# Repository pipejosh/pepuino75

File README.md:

## Introducing the pepuino75

This is the pepuino75, a 75 percent keyboard, featuring my custom microcontroler, the pepuinoNanoV1 (https://github.com/pipejosh/pepuinoNano-devBoard), this keyboard also features a rotary encoder, design to make it as compact as possible, without lossing any of its features!

### RENDER
 
### SCHEMATIC
 
### PCB
 
### CASE

### BOM

## KIT Components

| Item | Description | Quantity | Unit Price | Total Price | URL |
|---|---|---:|---:|---:|---|
| Keycaps Set | Keycaps for the keyboard | 126 | 0.07 | 8.31 | https://www.aliexpress.com/item/1005007321700850.html |
| Switches | Mechanical switches | 90 | 0.20 | 18.11 | https://www.aliexpress.com/item/1005009787231480.html |
| Diodes | SMD diodes | 100 | 0.03 | 3.15 | https://www.aliexpress.com/item/1005007160563285.html |
| USB-C Cable | USB-C cable | 1 | 3.31 | 3.31 | https://www.aliexpress.com/item/1005005080440661.html |
| M2 Standoff | M2 standoff 5 mm | 50 | 0.05 | 2.50 | https://www.aliexpress.com/item/1005006049595637.html |
| M2 Screw | M2 screw 5 mm | 50 | 0.03 | 1.60 | https://www.aliexpress.com/item/1005005070119421.html |
| Stabilizers | MX stabilizers (6.25u & 2u) | 5 | 0.73 | 3.64 | https://www.aliexpress.com/item/1005007212869086.html |
| Taxes | AliExpress tax | — | — | 4.28 | — |

**KIT Components Subtotal:** 44.90

---

## PCB Costs

| Item | Description | Cost |
|---|---|---:|
| JLCPCB | Pepuino75 PCB | 26.47 |
| JLCPCB Shipping | PCB shipping + taxes | 21.58 |

**PCB Subtotal:** 48.05

---

## GRAND TOTAL

| Category | Amount |
|---|---:|
| KIT Components | 44.90 |
| PCB | 48.05 |
| **TOTAL** | **92.95** |

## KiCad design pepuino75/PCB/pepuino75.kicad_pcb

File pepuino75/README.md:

## Introducing the pepuino75

This is the pepuino75, a 75 percent keyboard, featuring my custom microcontroler, the pepuinoNanoV1, this keyboard also features a rotary encoder, design to make it as compact as possible, without lossing any of its features!

### BOM
 
### SCHEMATIC
 
### PCB
 
### RENDER

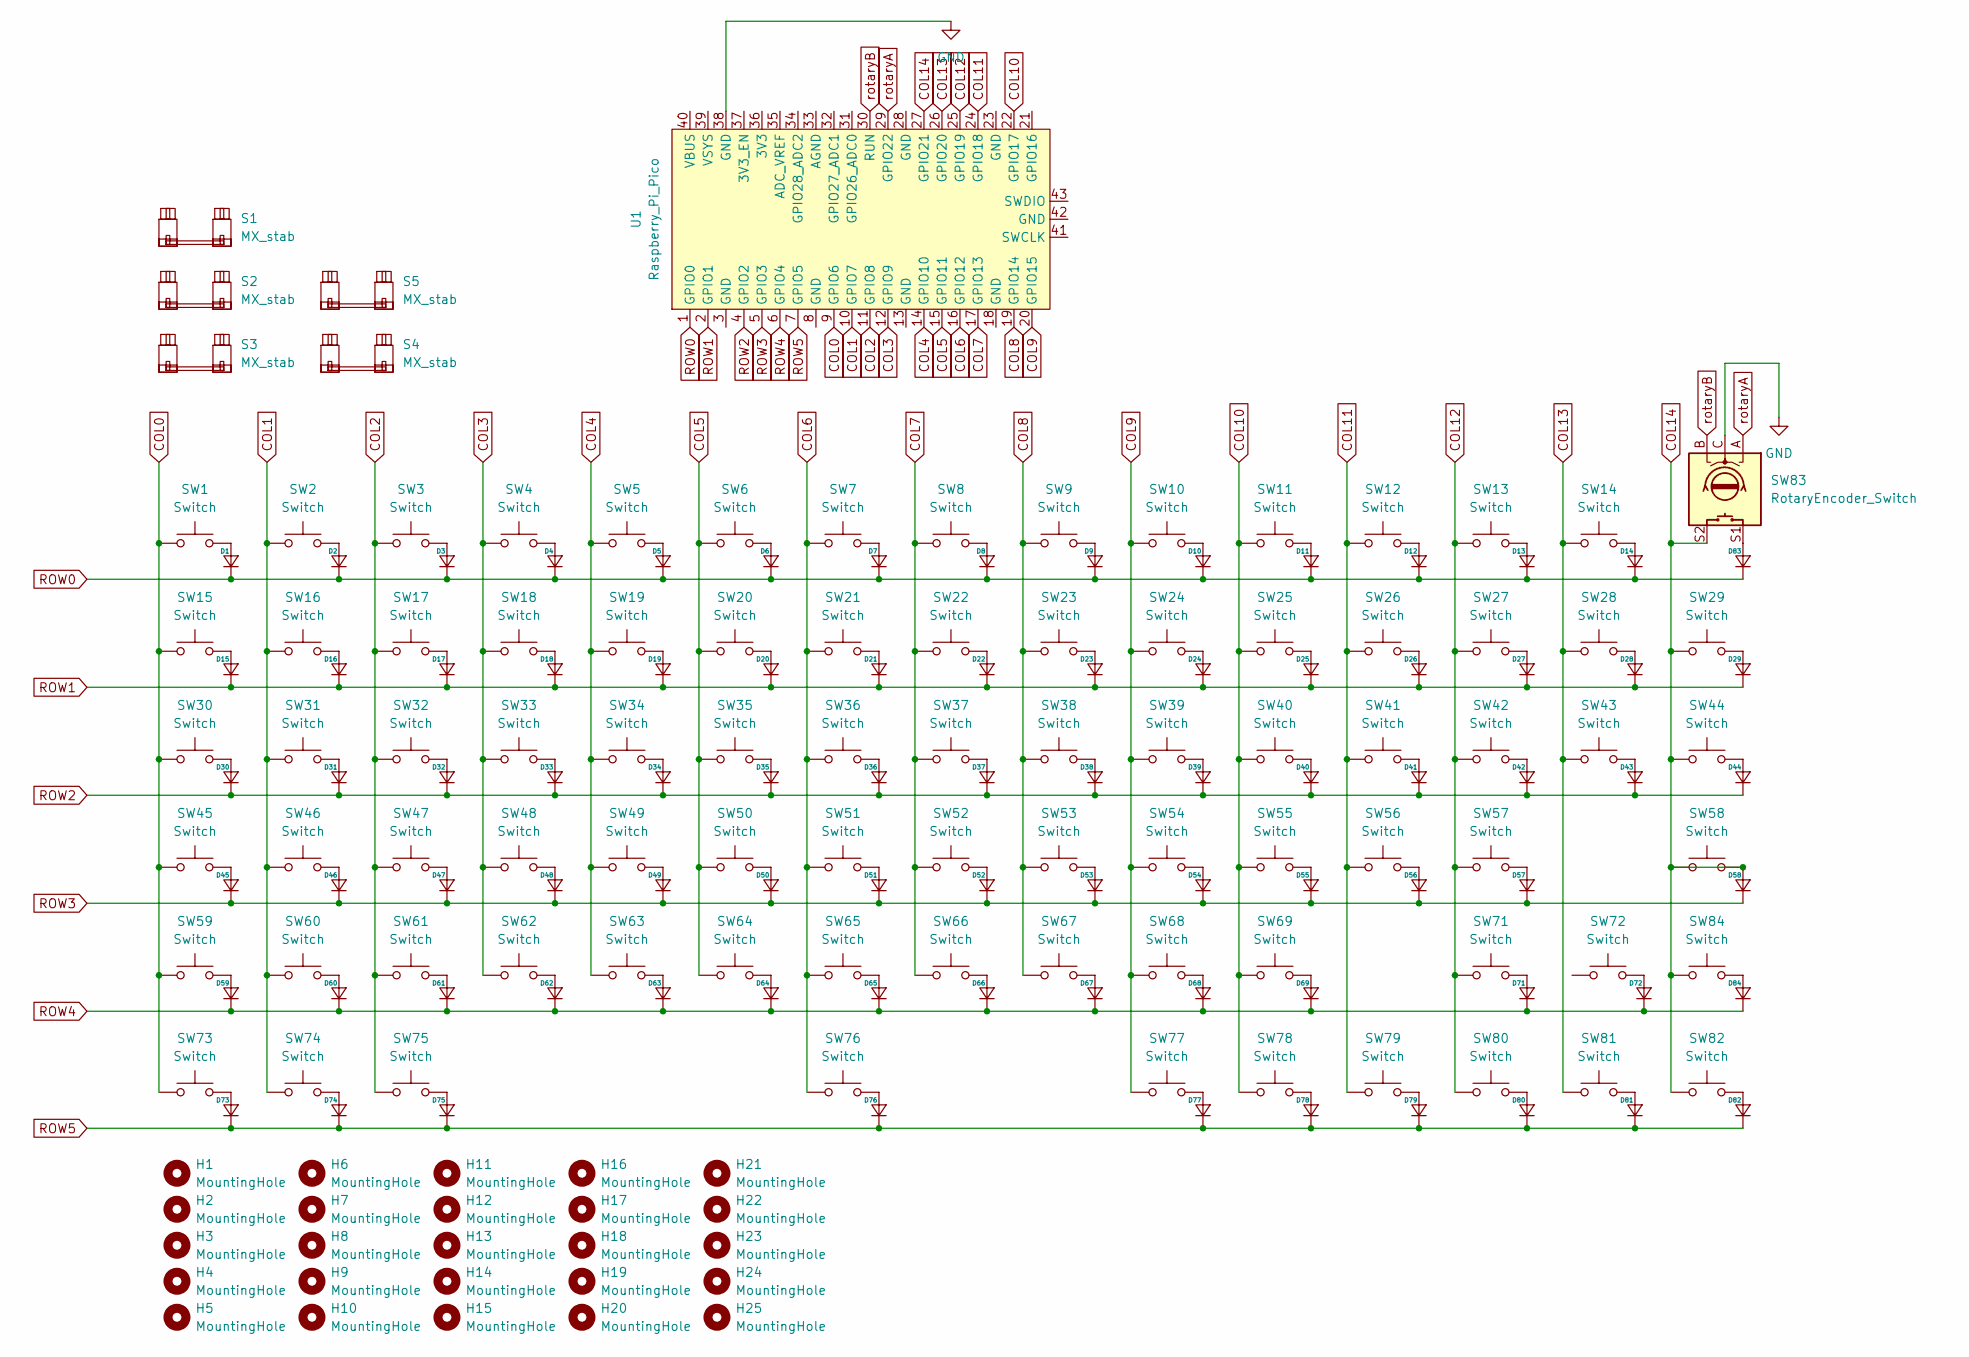
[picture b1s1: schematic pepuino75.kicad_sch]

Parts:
D1, D2, D3, D4, D5, D6, D7, D8, D9, D10, D11, D12, D13, D14, D15, D16, D17, D18, D19, D20, D21, D22, D23, D24, D25, D26, D27, D28, D29, D30, D31, D32, D33, D34, D35, D36, D37, D38, D39, D40, D41, D42, D43, D44, D45, D46, D47, D48, D49, D50, D51, D52, D53, D54, D55, D56, D57, D58, D59, D60, D61, D62, D63, D64, D65, D66, D67, D68, D69, D71, D72, D73, D74, D75, D76, D77, D78, D79, D80, D81, D82, D83, D84: Diode_SOD-123
H1, H2, H3, H4, H5, H6, H7, H8, H9, H10, H11, H12, H13, H14, H15, H16, H17, H18, H19, H20, H21, H22, H23, H24, H25: MountingHole; MountingHole_2.2mm_M2
S1: MX_stab; Stabilizer_MX_6.25u
S2, S3, S4, S5: MX_stab; Stabilizer_MX_2.00u
SW1, SW2, SW3, SW4, SW5, SW6, SW7, SW8, SW9, SW10, SW11, SW12, SW13, SW14, SW15, SW16, SW17, SW18, SW19, SW20, SW21, SW22, SW23, SW24, SW25, SW26, SW27, SW29, SW31, SW32, SW33, SW34, SW35, SW36, SW37, SW38, SW39, SW40, SW41, SW42, SW44, SW46, SW47, SW48, SW49, SW50, SW51, SW52, SW53, SW54, SW55, SW56, SW58, SW60, SW61, SW62, SW63, SW64, SW65, SW66, SW67, SW68, SW69, SW72, SW77, SW78, SW79, SW80, SW81, SW82, SW84: Switch; MX_PCB_1.00u
SW28: Switch; MX_PCB_2.00u
SW30, SW43: Switch; MX_PCB_1.50u
SW45, SW71: Switch; MX_PCB_1.75u
SW57, SW59: Switch; MX_PCB_2.25u
SW73, SW74, SW75: Switch; MX_PCB_1.25u
SW76: Switch; MX_PCB_6.25u
SW83: RotaryEncoder_Switch; ROT_Alps_EC11E-Switch
U1: Raspberry_Pi_Pico

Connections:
COL0: SW1.1, SW15.1, SW30.1, SW45.1, SW59.1, SW73.1, U1.9 (GPIO6)
COL1: SW2.1, SW16.1, SW31.1, SW46.1, SW60.1, SW74.1, U1.10 (GPIO7)
COL2: SW3.1, SW17.1, SW32.1, SW47.1, SW61.1, SW75.1, U1.11 (GPIO8)
COL3: SW4.1, SW18.1, SW33.1, SW48.1, SW62.1, U1.12 (GPIO9)
COL4: SW5.1, SW19.1, SW34.1, SW49.1, SW63.1, U1.14 (GPIO10)
COL5: SW6.1, SW20.1, SW35.1, SW50.1, SW64.1, U1.15 (GPIO11)
COL6: SW7.1, SW21.1, SW36.1, SW51.1, SW65.1, SW76.1, U1.16 (GPIO12)
COL7: SW8.1, SW22.1, SW37.1, SW52.1, SW66.1, U1.17 (GPIO13)
COL8: SW9.1, SW23.1, SW38.1, SW53.1, SW67.1, U1.19 (GPIO14)
COL9: SW10.1, SW24.1, SW39.1, SW54.1, SW68.1, SW77.1, U1.20 (GPIO15)
COL10: SW11.1, SW25.1, SW40.1, SW55.1, SW69.1, SW78.1, U1.22 (GPIO17)
COL11: SW12.1, SW26.1, SW41.1, SW56.1, SW79.1, U1.24 (GPIO18)
COL12: SW13.1, SW27.1, SW42.1, SW57.1, SW71.1, SW80.1, U1.25 (GPIO19)
COL13: SW14.1, SW28.1, SW43.1, SW81.1, U1.26 (GPIO20)
COL14: D58.2 (A), SW29.1, SW44.1, SW58.1, SW58.2, SW82.1, SW83.S2, SW84.1, U1.27 (GPIO21)
GND: SW83.C, U1.38 (GND)
unnamed: D1.2 (A), SW1.2
unnamed: D2.2 (A), SW2.2
unnamed: D3.2 (A), SW3.2
unnamed: D4.2 (A), SW4.2
unnamed: D5.2 (A), SW5.2
unnamed: D6.2 (A), SW6.2
unnamed: D7.2 (A), SW7.2
unnamed: D8.2 (A), SW8.2
unnamed: D9.2 (A), SW9.2
unnamed: D10.2 (A), SW10.2
unnamed: D11.2 (A), SW11.2
unnamed: D12.2 (A), SW12.2
unnamed: D13.2 (A), SW13.2
unnamed: D14.2 (A), SW14.2
unnamed: D15.2 (A), SW15.2
unnamed: D16.2 (A), SW16.2
unnamed: D17.2 (A), SW17.2
unnamed: D18.2 (A), SW18.2
unnamed: D19.2 (A), SW19.2
unnamed: D20.2 (A), SW20.2
unnamed: D21.2 (A), SW21.2
unnamed: D22.2 (A), SW22.2
unnamed: D23.2 (A), SW23.2
unnamed: D24.2 (A), SW24.2
unnamed: D25.2 (A), SW25.2
unnamed: D26.2 (A), SW26.2
unnamed: D27.2 (A), SW27.2
unnamed: D28.2 (A), SW28.2
unnamed: D29.2 (A), SW29.2
unnamed: D30.2 (A), SW30.2
unnamed: D31.2 (A), SW31.2
unnamed: D32.2 (A), SW32.2
unnamed: D33.2 (A), SW33.2
unnamed: D34.2 (A), SW34.2
unnamed: D35.2 (A), SW35.2
unnamed: D36.2 (A), SW36.2
unnamed: D37.2 (A), SW37.2
unnamed: D38.2 (A), SW38.2
unnamed: D39.2 (A), SW39.2
unnamed: D40.2 (A), SW40.2
unnamed: D41.2 (A), SW41.2
unnamed: D42.2 (A), SW42.2
unnamed: D43.2 (A), SW43.2
unnamed: D44.2 (A), SW44.2
unnamed: D45.2 (A), SW45.2
unnamed: D46.2 (A), SW46.2
unnamed: D47.2 (A), SW47.2
unnamed: D48.2 (A), SW48.2
unnamed: D49.2 (A), SW49.2
unnamed: D50.2 (A), SW50.2
unnamed: D51.2 (A), SW51.2
unnamed: D52.2 (A), SW52.2
unnamed: D53.2 (A), SW53.2
unnamed: D54.2 (A), SW54.2
unnamed: D55.2 (A), SW55.2
unnamed: D56.2 (A), SW56.2
unnamed: D57.2 (A), SW57.2
unnamed: D59.2 (A), SW59.2
unnamed: D60.2 (A), SW60.2
unnamed: D61.2 (A), SW61.2
unnamed: D62.2 (A), SW62.2
unnamed: D63.2 (A), SW63.2
unnamed: D64.2 (A), SW64.2
unnamed: D65.2 (A), SW65.2
unnamed: D66.2 (A), SW66.2
unnamed: D67.2 (A), SW67.2
unnamed: D68.2 (A), SW68.2
unnamed: D69.2 (A), SW69.2
unnamed: D71.2 (A), SW71.2
unnamed: D72.2 (A), SW72.2
unnamed: D73.2 (A), SW73.2
unnamed: D74.2 (A), SW74.2
unnamed: D75.2 (A), SW75.2
unnamed: D76.2 (A), SW76.2
unnamed: D77.2 (A), SW77.2
unnamed: D78.2 (A), SW78.2
unnamed: D79.2 (A), SW79.2
unnamed: D80.2 (A), SW80.2
unnamed: D81.2 (A), SW81.2
unnamed: D82.2 (A), SW82.2
unnamed: D83.2 (A), SW83.S1
unnamed: D84.2 (A), SW84.2
ROW0: D1.1 (K), D2.1 (K), D3.1 (K), D4.1 (K), D5.1 (K), D6.1 (K), D7.1 (K), D8.1 (K), D9.1 (K), D10.1 (K), D11.1 (K), D12.1 (K), D13.1 (K), D14.1 (K), D83.1 (K), U1.1 (GPIO0)
ROW1: D15.1 (K), D16.1 (K), D17.1 (K), D18.1 (K), D19.1 (K), D20.1 (K), D21.1 (K), D22.1 (K), D23.1 (K), D24.1 (K), D25.1 (K), D26.1 (K), D27.1 (K), D28.1 (K), D29.1 (K), U1.2 (GPIO1)
ROW2: D30.1 (K), D31.1 (K), D32.1 (K), D33.1 (K), D34.1 (K), D35.1 (K), D36.1 (K), D37.1 (K), D38.1 (K), D39.1 (K), D40.1 (K), D41.1 (K), D42.1 (K), D43.1 (K), D44.1 (K), U1.4 (GPIO2)
ROW3: D45.1 (K), D46.1 (K), D47.1 (K), D48.1 (K), D49.1 (K), D50.1 (K), D51.1 (K), D52.1 (K), D53.1 (K), D54.1 (K), D55.1 (K), D56.1 (K), D57.1 (K), D58.1 (K), U1.5 (GPIO3)
ROW4: D59.1 (K), D60.1 (K), D61.1 (K), D62.1 (K), D63.1 (K), D64.1 (K), D65.1 (K), D66.1 (K), D67.1 (K), D68.1 (K), D69.1 (K), D71.1 (K), D72.1 (K), D84.1 (K), U1.6 (GPIO4)
ROW5: D73.1 (K), D74.1 (K), D75.1 (K), D76.1 (K), D77.1 (K), D78.1 (K), D79.1 (K), D80.1 (K), D81.1 (K), D82.1 (K), U1.7 (GPIO5)
rotaryA: SW83.A, U1.29 (GPIO22)
rotaryB: SW83.B, U1.30 (RUN)

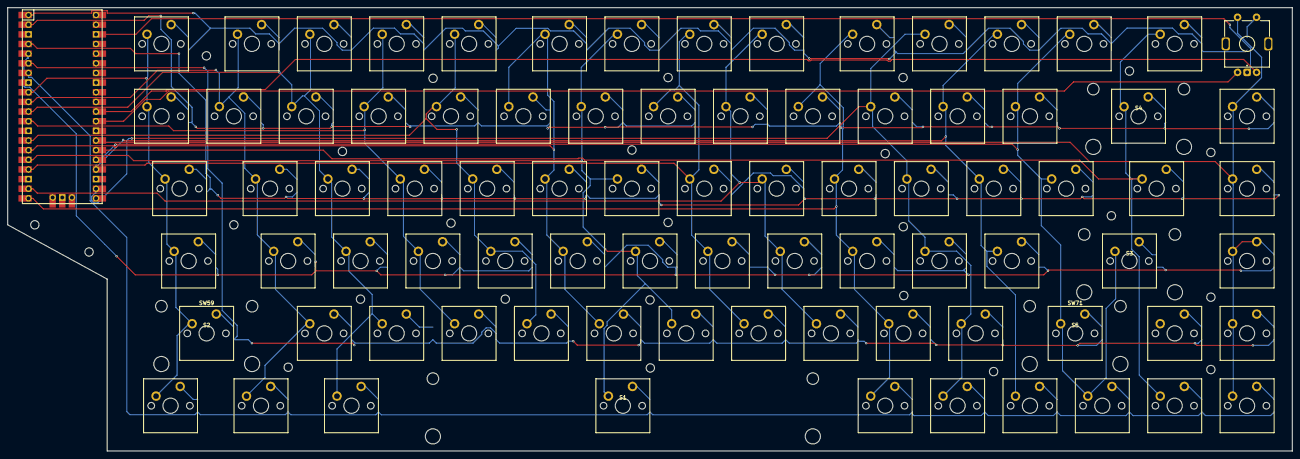
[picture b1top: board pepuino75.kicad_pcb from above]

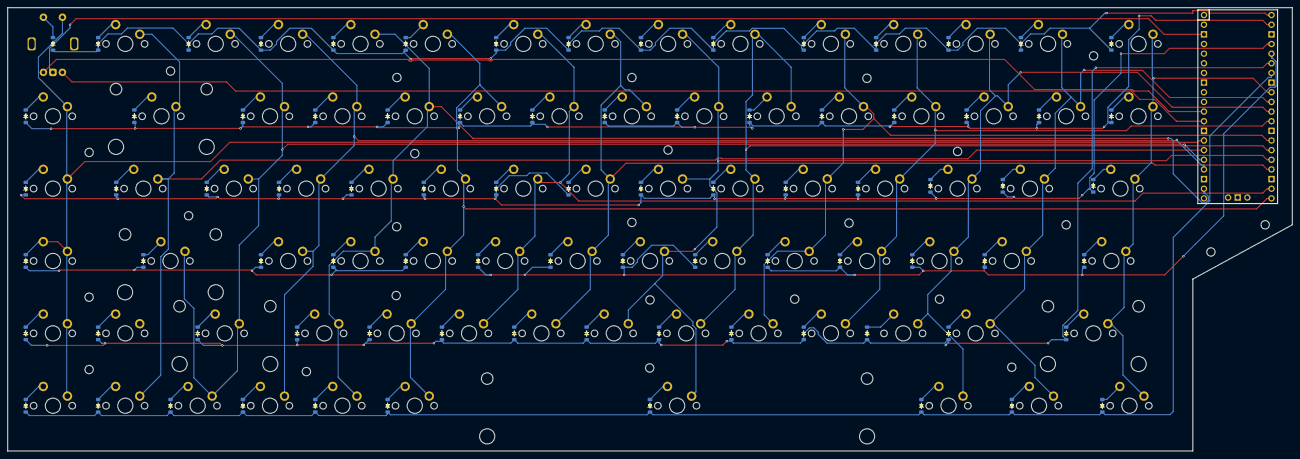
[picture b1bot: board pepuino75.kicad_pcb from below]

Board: 2 copper layers, 338.1 x 116.7 mm, 197 parts (83 on the bottom side), 106 nets.

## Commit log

2026-01-06 project files
2026-01-06 Update README with additional notes and images
2026-01-14 add firmware + add new images + redesign the case
2026-01-25 Revise README structure and update BOM details
    Reorganized sections in README for clarity and updated BOM with detailed item descriptions and URLs.
2026-01-25 Revise README for improved structure and clarity
    Updated the README to enhance formatting and clarity, including a structured BOM and PCB costs section.
